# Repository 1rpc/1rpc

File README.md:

# One Robot Per Child - Main Repository

__*One robot per child* is a german initiave startet from makerspace Bonn to increase technical scills of german pupils. So at the moment the  project is complely described and documented only in german language!__

In diesem Repository sind alle Informationen gebündelt, die man benötigt um mit unserem Kit eigene Projekte umzusetzen und vorhandene Informationen zu erhalten. 

***One Robot per Child*** ist eine Initiative des [MakerspaceBonn e. V.]() die am 1. Oktober 2021 in der Umsetzung startet. Die Initiative verfolgt das Ziel die MINT-Bildung (Mathematik, Informatik, Naturwissenschaften und Technik ) für alle Schülerinnen und Schüler in Deutschland zu verbessern. 
***One Robot per Child*** ist eine offene MINT-Lernplattform, die Menschen aller Altersgruppen (realistisch ab  ca. 9 Jahren - also wenn Ihr schreibe und  lesen könnt sowie die Grundrechenarten beherrscht, Freude und Spass am Konstruieren, Programmieren und Erfinden habt). Alle Teile sind Open Source, so dass  sie für Lehr- und Lernzwecke bedenkenlos verwendet werden können.

Weitere Informationen kann man auf der [Homepage: https://www.1rpc.de/](https://www.1rpc.de) erhalten.

__!!!Achtung !!!__ 

__Zusätzlich zu diesem Repository werden weitere Repositories benötigt, um mit dem Toolkit arbeiten zu können.__

# Installation 

Die Installationsanweisung befindet sich unter: [https://www.1rpc.de/index.php/portfolio/die-technik-im-projekt/eigene-projekte-entwerfen](https://www.1rpc.de/index.php/portfolio/die-technik-im-projekt/eigene-projekte-entwerfen)

# Einführung

Die meisten Menschen, die nach dem zweiten Weltkrieg geboren wurden haben schon mal mit Lego, Fischertechnik, Märklinmetall oder vergleichbaren Technikbaukästen gespielt. Mit diesen Bauteilsystemen ist es möglich eigene Ideen aus Grundbausteinen zusammenzusetzen. Allerdings haben diese Systeme auch ihre Grenzen. Die Geräte und Maschinen die man damit bauen kann sind weder halt- noch belastbar. Außerdem erlauben alle diese Systeme nur Kreativität innerhalb des eigenen Systems. Die Grundideen sind schon sehr alt: Märklinmetall - 1919, Legobaustein - 1958, Fischertechnik - 1965. Durch die rasante Entwicklung der Technik in Verbindung mit Open Source Programmen sind heute Techniken für jedermann verfügbar, die es uns erlauben Geräte zu designen und zu bauen ohne auf obige Krücken angewiesen zu sein. Folgende Techniken stehen heute fast jedem Menschen zur Verfügung:

- Computer
- 3D-Drucker
- CNC-Fräsen
- Laser-Plotter
- Open-Source-Programme:
  - CAD-Programme
  - CAE-Programme
  - Designprogramme
  - Tools
  - Programmierumgebungen

Allerdings muß man mit diesen Tools auch lernen umzugehen. Man braucht Vorlagen, Anleitung und einen einfachen Zugang. 

# Start

Der einfachste Start ist einer unserer Roboter. Robo-1 oder Robo-X. 

# Teile des Systems

One Robot per Child nutzt auf der einen Seite günstige Hardware, die man üblicherweise bei elektronikversendern oder im Internet leicht beziehen kann und auf der anderen Seite entweder Halbzeuge, die im Baumarkt erhält,lich sind und auf der anderen Seite Teile, die im 3d-Drucker hergestellt werden. Ein typisches Projekt besteht also aus :

- Elektronik,
- Mechanik und Software

## Elektronik

## Mechanik

### Fertigteile 

Viele Teile sind als Fertigteile direkt nutzbar. Beispielsweise nutzen wir folgende Teile:

- 20mm Aluminiumprofile 
- Kugellager
- Zahnriemen mit passenden Zahnrädern
- Motoren:
  - Nema 17 Schrittmotoren
  - N20 Getriebemotoren
  - Die Gelben Getriebemotoren

### Halbzeuge

Alles was man für ein paar Euros im örtlichen Baumarkt kaufen kann, kann, man für den Bau bei One Robot per Child verwenden. Z. B. Bretter, Schrauben, 

### Teile aus dem 3d-Drucker

Viele komplexe Teile können wir selbst mit einem 3d-Drucker herstellen. Diese Teile sind hier im Repository veröffentlicht. Das sind z. B. unsere Construction Cubes oder auch Motorhalter oder Laufräder. Alle Teile sind als OpenSCAD-Modell direkt verwendbar und sowohl als Modell wie auch als STL-Datei im Repository hinterlegt.

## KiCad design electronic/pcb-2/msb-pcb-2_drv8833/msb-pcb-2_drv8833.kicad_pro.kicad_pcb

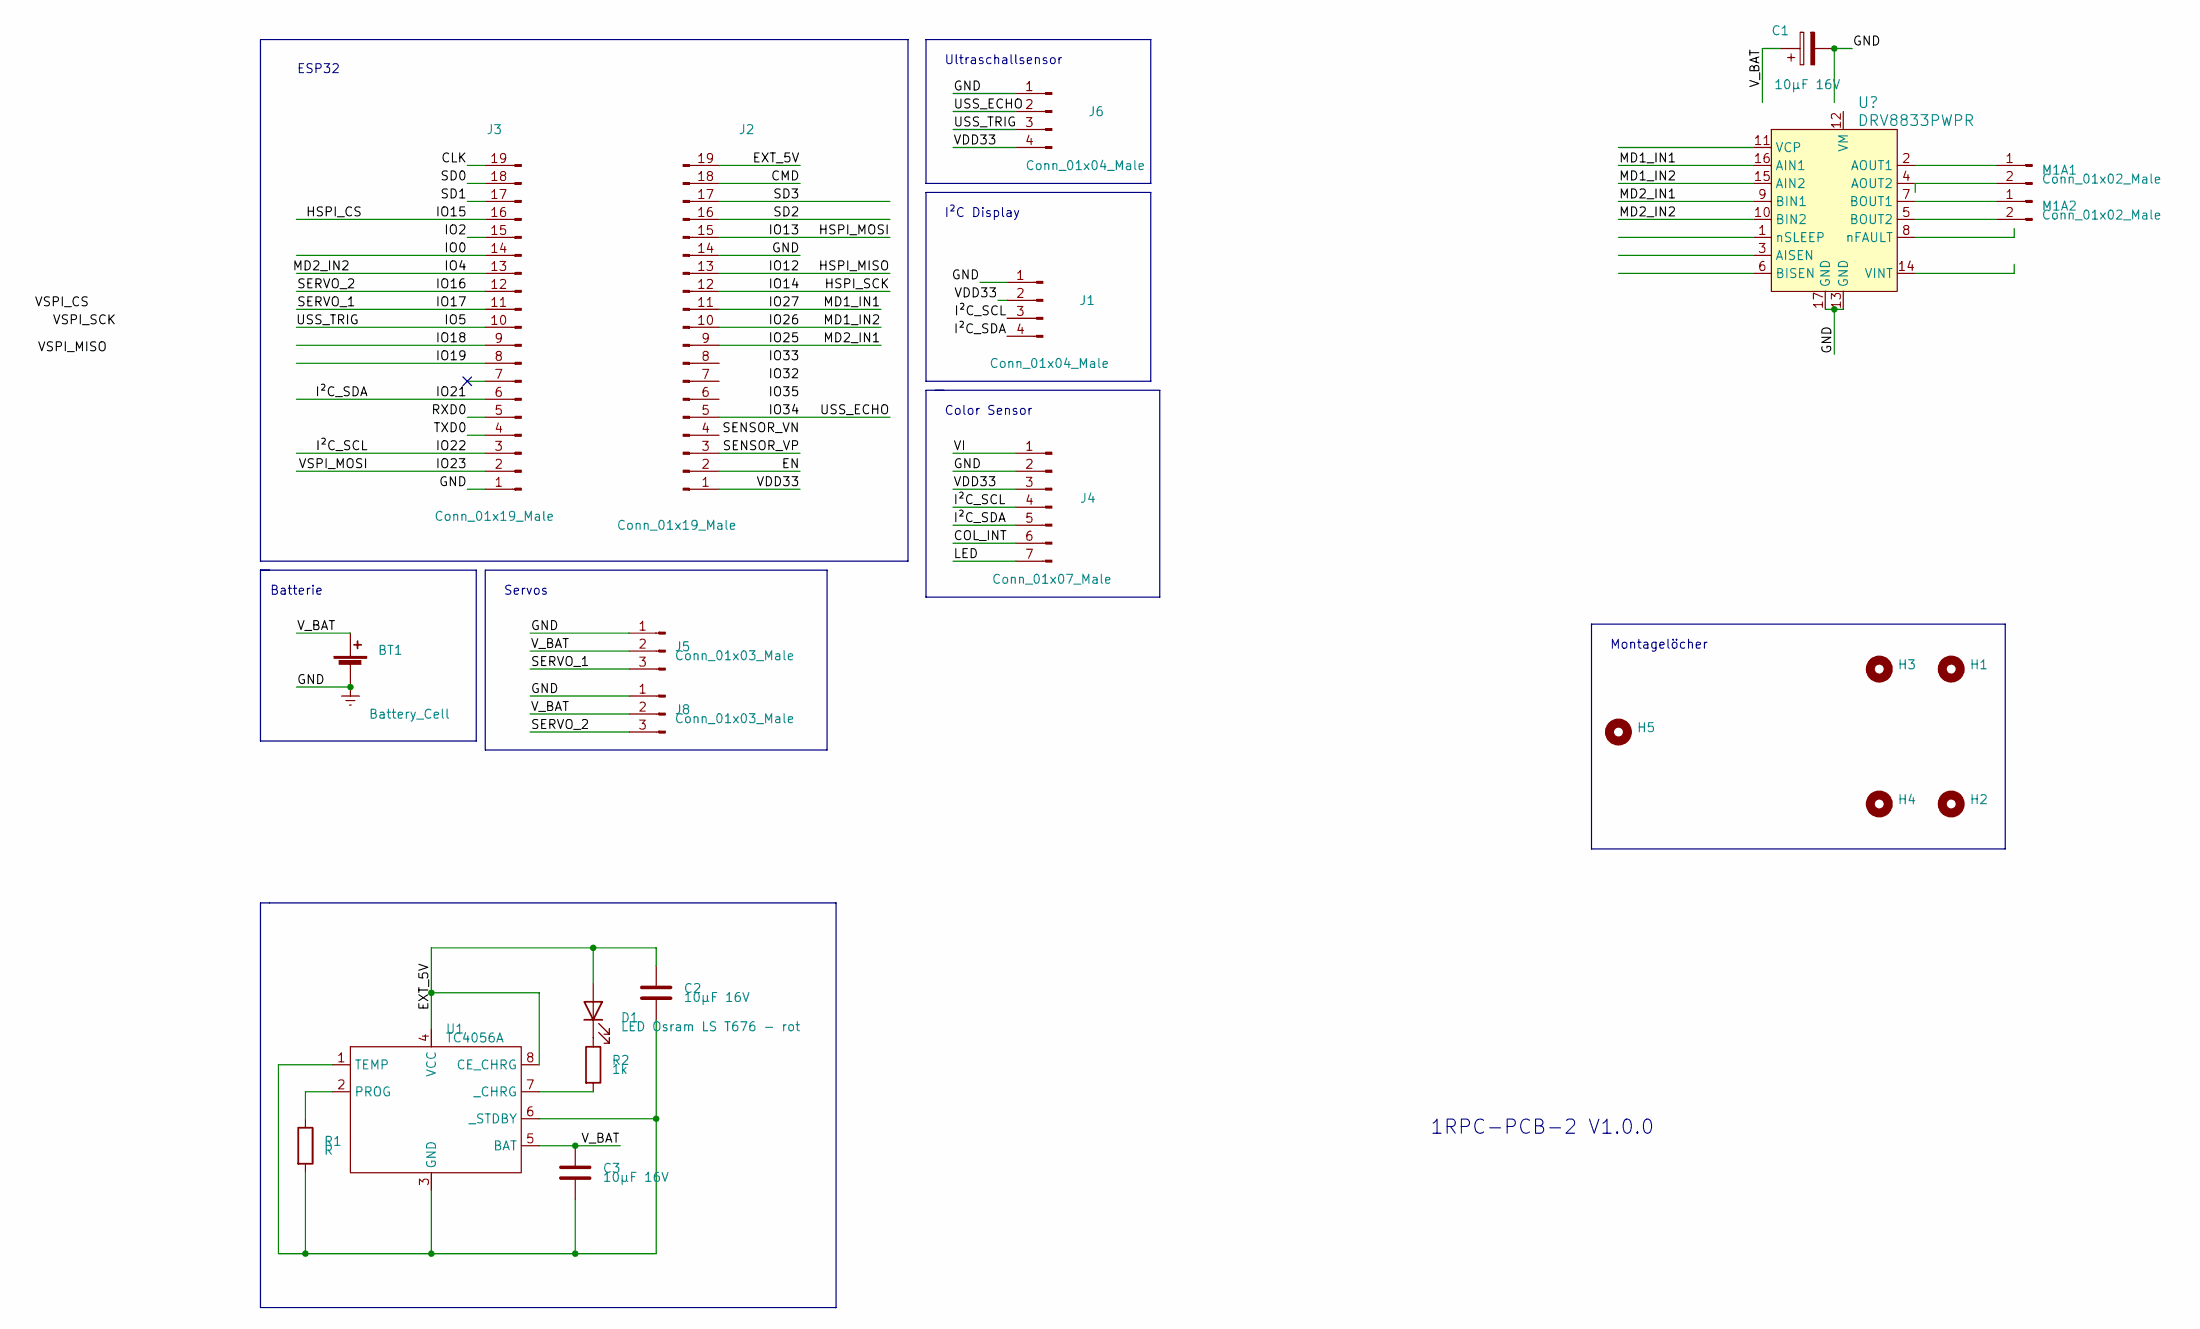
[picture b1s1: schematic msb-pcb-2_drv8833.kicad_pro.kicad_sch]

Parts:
BT1: Battery_Cell; BatteryHolder_Keystone_1042_1x18650
C1: 10µF 16V; CP_Elec_6.3x7.7
C2, C3: 10µF 16V; CP_Elec_6.3x3
D1: LED Osram LS T676 - rot; LED_PLCC-2
H1, H2, H3, H4: MountingHole; MountingHole_2.2mm_M2_DIN965_Pad_TopBottom
H5: MountingHole; MountingHole_3.2mm_M3
J1: Conn_01x04_Male; JST_XH_B4B-XH-A_1x04_P2.50mm_Vertical
J2, J3: Conn_01x19_Male; PinSocket_1x19_P2.54mm_Vertical
J4: Conn_01x07_Male; JST_XH_B7B-XH-A_1x07_P2.50mm_Vertical
J5, J8: Conn_01x03_Male; JST_XH_B3B-XH-A_1x03_P2.50mm_Vertical
J6: Conn_01x04_Male; PinSocket_1x04_P2.54mm_Vertical
M1A1, M1A2: Conn_01x02_Male; JST_XH_B2B-XH-A_1x02_P2.50mm_Vertical
R1: R; R_0805_2012Metric
R2: 1k; R_0805_2012Metric
U1: TC4056A; SOIC-8-1EP_3.9x4.9mm_P1.27mm_EP2.41x3.81mm

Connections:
/CLK: J3.19
/CMD: J2.18
/COL_INT: J4.6
/EN: J2.2
/EXT_5V: C2.1, D1.2 (A), J2.19, U1.4 (VCC), U1.8 (CE_CHRG)
/HSPI_CS: J3.16
/HSPI_MISO: J2.13
/HSPI_MOSI: J2.15
/HSPI_SCK: J2.12
/IO0: J3.14
/IO2: J3.15
/IO4: J3.13; also elsewhere on the board
/IO5: J3.10, J6.3
/IO16: J3.12, J8.3
/IO17: J3.11, J5.3
/IO18: J3.9
/IO19: J3.8
/IO21: J1.4, J3.6, J4.5
/IO22: J1.3, J3.3, J4.4
/IO23: J3.2
/IO25: J2.9; also elsewhere on the board
/IO26: J2.10; also elsewhere on the board
/IO27: J2.11; also elsewhere on the board
/IO34: J2.5, J6.2
/LED: J4.7
/RXD0: J3.5
/SD0: J3.18
/SD1: J3.17
/SD2: J2.16
/SD3: J2.17
/SENSOR_VP: J2.3
/TXD0: J3.4
/VDD33: J1.2, J2.1, J4.3, J6.4
/VI: J4.1
/V_BAT: BT1.1 (+), C1.1, C3.1, J5.2, J8.2, U1.5 (BAT); also elsewhere on the board
Earth: BT1.2 (-), C1.2, J1.1, J2.14, J3.1, J4.2, J5.1, J6.1, J8.1; also elsewhere on the board
unnamed: D1.1 (K), R2.1
unnamed 37: M1A1.1; also elsewhere on the board
unnamed 38: M1A1.2; also elsewhere on the board
unnamed 39: M1A2.1; also elsewhere on the board
unnamed 40: M1A2.2; also elsewhere on the board
unnamed: C2.2, C3.2, R1.2, U1.1 (TEMP), U1.3 (GND), U1.6 (_STDBY)
unnamed: R1.1, U1.2 (PROG)
unnamed: R2.2, U1.7 (_CHRG)

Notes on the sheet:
I²C Display
Montagelöcher
1RPC-PCB-2 V1.0.0
Servos
Ultraschallsensor
Color Sensor
ESP32
Batterie

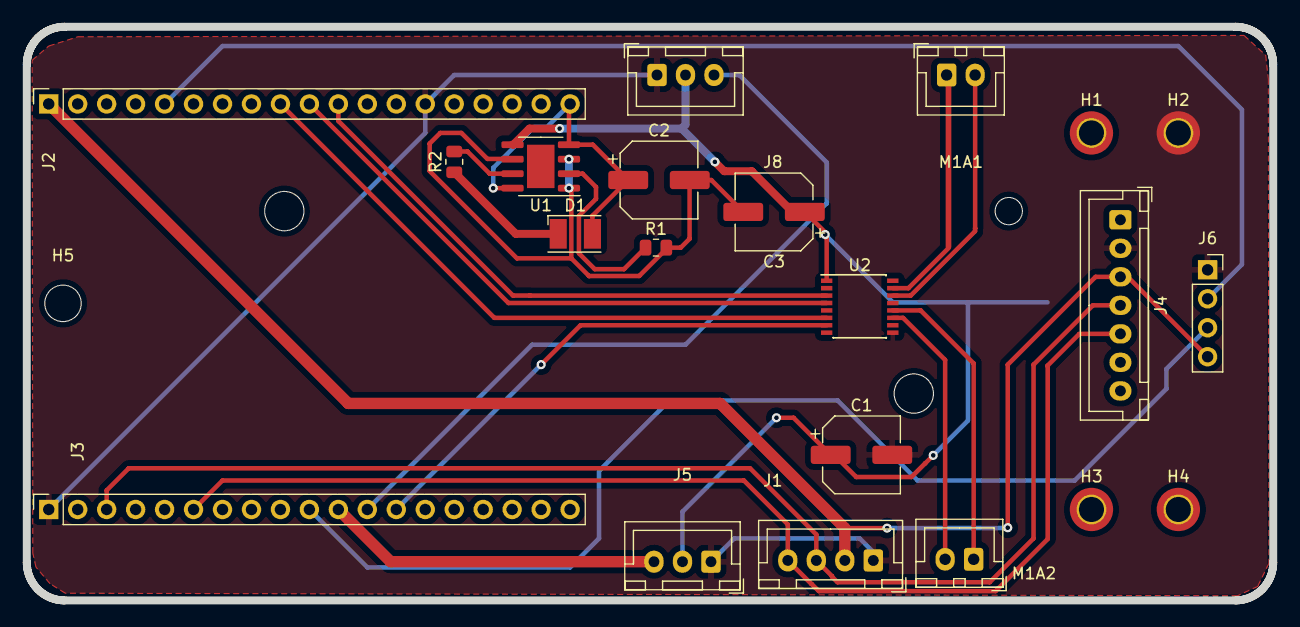
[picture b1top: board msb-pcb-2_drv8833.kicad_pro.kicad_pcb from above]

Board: 2 copper layers, 109.3 x 50.3 mm, 23 parts (1 on the bottom side), 22 nets.

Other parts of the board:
U2: LB1973JA; SSOP-16_4.4x5.2mm_P0.65mm

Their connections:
/IO4: U2.7 (IN2); also elsewhere on the board
/IO25: U2.6 (IN1); also elsewhere on the board
/IO26: U2.4 (IN3); also elsewhere on the board
/IO27: U2.3 (IN4); also elsewhere on the board
/V_BAT: U2.1 (VCC); also elsewhere on the board
Earth: U2.9 (GND); also elsewhere on the board
unnamed 37: U2.15 (OUT4); also elsewhere on the board
unnamed 38: U2.14 (OUT3); also elsewhere on the board
unnamed 39: U2.12 (OUT1); also elsewhere on the board
unnamed 40: U2.11 (OUT2); also elsewhere on the board

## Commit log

2022-04-02 first Checkin
2022-04-02 Version of KiCad-Files Change
